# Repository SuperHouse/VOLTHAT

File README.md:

Voltage Regulator Hat for Raspberry Pi
=======================================
Designed by Nick Fryer and Jonathan Oxer

FEATURES
--------

Supply power via screw terminals, 2.1mm DC jack, or the PoE header on
Raspberry Pi 3 B+. Regulates down to 5V to supply the Raspberry Pi.

 * I2C header for OLED.
 * I2C-BREAKOUT header.
 * Prototyping area.

INSTALLATION
------------
The design is saved as an EAGLE project. EAGLE PCB design software is
available from www.cadsoftusa.com free for non-commercial use. To use
this project download it and place the directory containing these files
into the "eagle" directory on your computer. Then open EAGLE and
navigate to the project.

DISTRIBUTION
------------
The specific terms of distribution of this project are governed by the
license referenced below.

LICENSE
-------
Licensed under the TAPR Open Hardware License (www.tapr.org/OHL).
The "license" folder within this repository also contains a copy of
this license in plain text format.

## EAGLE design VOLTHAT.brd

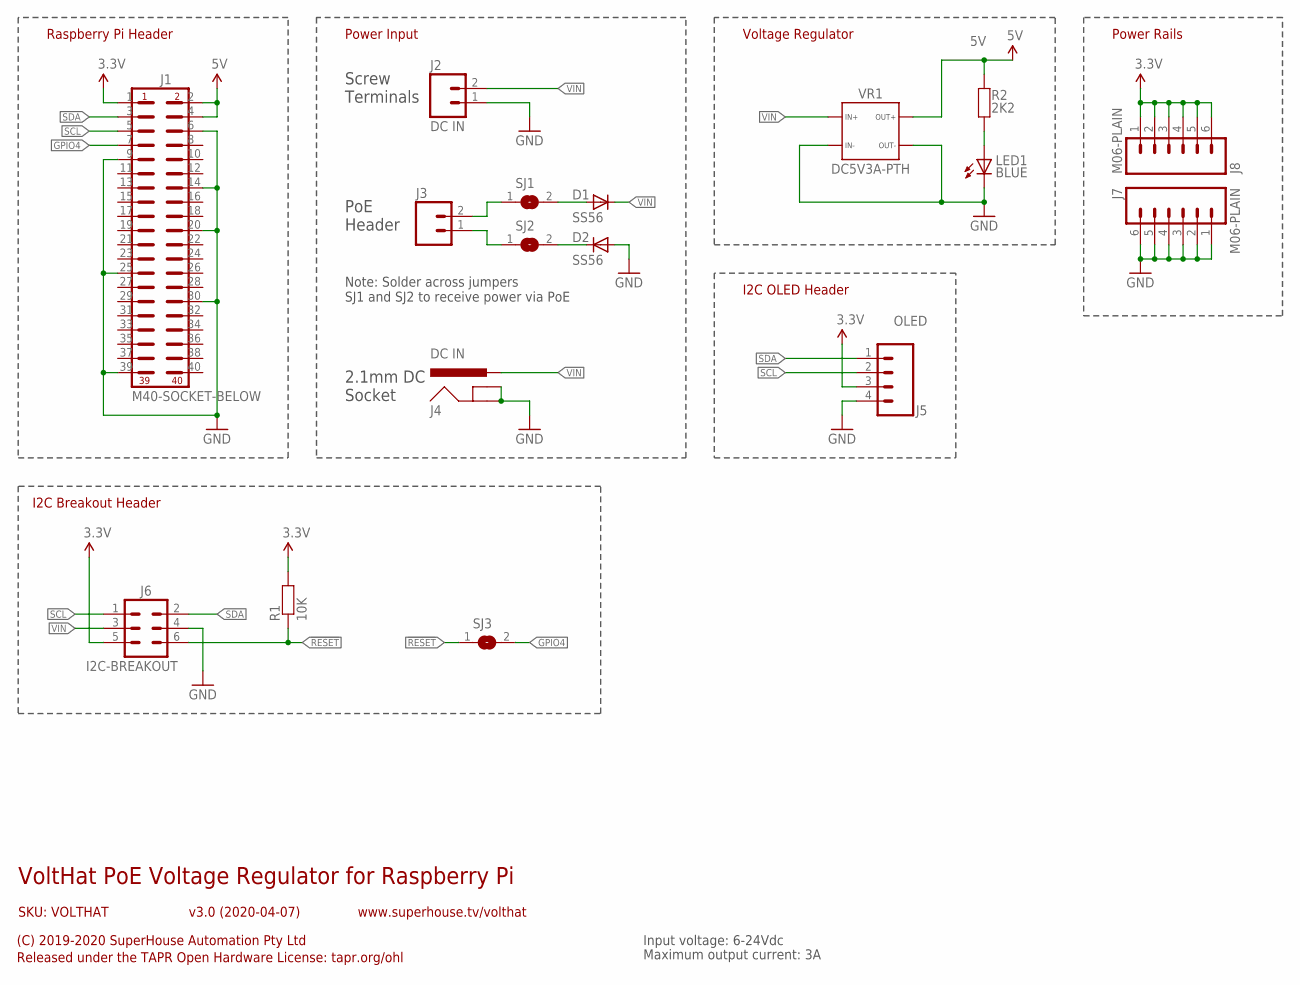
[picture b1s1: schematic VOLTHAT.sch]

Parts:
D1, D2: SS56; SMA-DIODE
J1: M40-SOCKET-BELOW; 2X20-S-BELOW
J2: DC IN; SCREWTERMINAL-3.5MM-2
J3: M02-SOCKET-BELOW; 1X02-S-BELOW
J4: DC IN; POWER_JACK_SLOTS
J5: OLED; 1X04
J6: I2C-BREAKOUT; 2X03-SHROUDED
J7, J8: M06-PLAIN; 1X06
LED1: BLUE; LED-0603
R1: 10K; R0603
R2: 2K2; R0603
SJ1, SJ2, SJ3: SJ-NORMAL; SJ
VR1: DC5V3A-PTH

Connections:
3.3V: J1.1, J5.3, J6.5, J8.1, J8.2, J8.3, J8.4, J8.5, J8.6, R1.2
5V: J1.2, J1.4, R2.1, VR1.3A (3), VR1.3B (3)
!RESET: J6.6, R1.1, SJ3.1
GND: D2.A, J1.6, J1.9, J1.14, J1.20, J1.25, J1.30, J1.39, J2.1, J4.GND, J4.GNDBREAK, J5.4, J6.4, J7.1, J7.2, J7.3, J7.4, J7.5, J7.6, LED1.C, VR1.1A (1), VR1.1B (1), VR1.4A (4), VR1.4B (4)
GPIO4: J1.7, SJ3.2
unnamed: J3.1, SJ2.1
unnamed: J3.2, SJ1.1
unnamed: D1.A, SJ1.2
unnamed: D2.C, SJ2.2
unnamed: LED1.A, R2.2
SCL: J1.5, J5.2, J6.1
SDA: J1.3, J5.1, J6.2
VIN: D1.C, J2.2, J4.PWR, J6.3, VR1.2A (2), VR1.2B (2)

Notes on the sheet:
VoltHat PoE Voltage Regulator for Raspberry Pi
v3.0 (2020-04-07)
(C) 2019-2020 SuperHouse Automation Pty Ltd
Released under the TAPR Open Hardware License: tapr.org/ohl
www.superhouse.tv/volthat
SKU: VOLTHAT
Raspberry Pi Header
Input voltage: 6-24Vdc
Maximum output current: 3A
Screw Terminals
PoE Header
2.1mm DC Socket
Power Input
I2C OLED Header
Power Rails
I2C Breakout Header
Voltage Regulator
Note: Solder across jumpers SJ1 and SJ2 to receive power via PoE

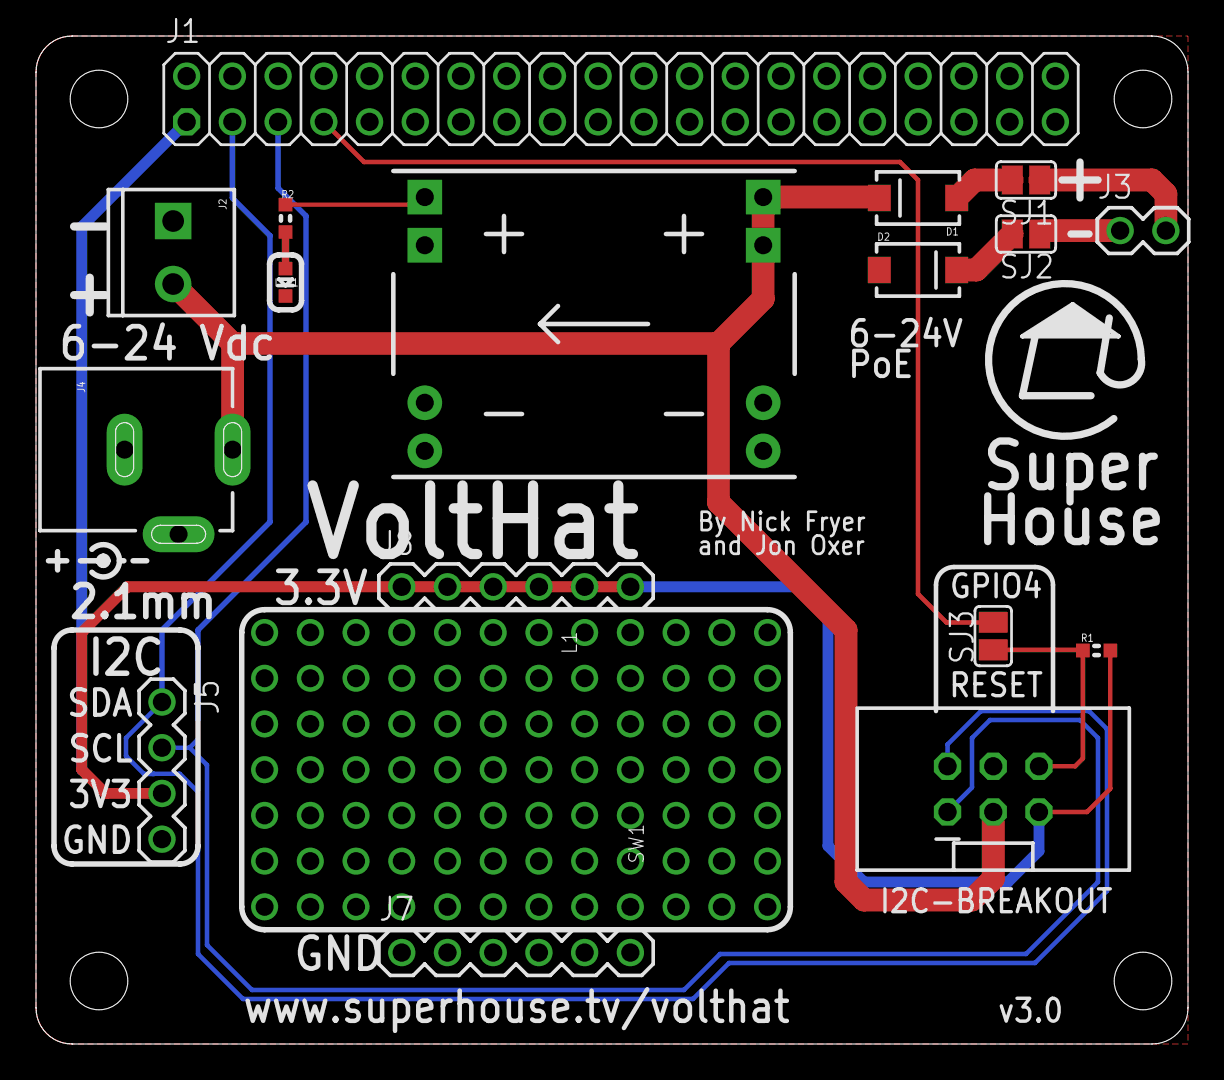
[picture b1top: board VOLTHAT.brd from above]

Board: 2 copper layers, 64.0 x 56.0 mm, 17 parts (0 on the bottom side), 13 nets.

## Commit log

2019-05-10 Initial project import
2019-05-15 Added header to take power from PoE on Raspberry Pi 3 B+
2019-05-23 Major routing for v1.0 release
2019-09-14 Major rework with 3A regulator module for v2.0 release
2020-04-08 Added I2C-BREAKOUT header for v3.0 release

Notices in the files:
VOLTHAT.brd:
Copyright 2019 SuperHouse Automation Pty Ltd
